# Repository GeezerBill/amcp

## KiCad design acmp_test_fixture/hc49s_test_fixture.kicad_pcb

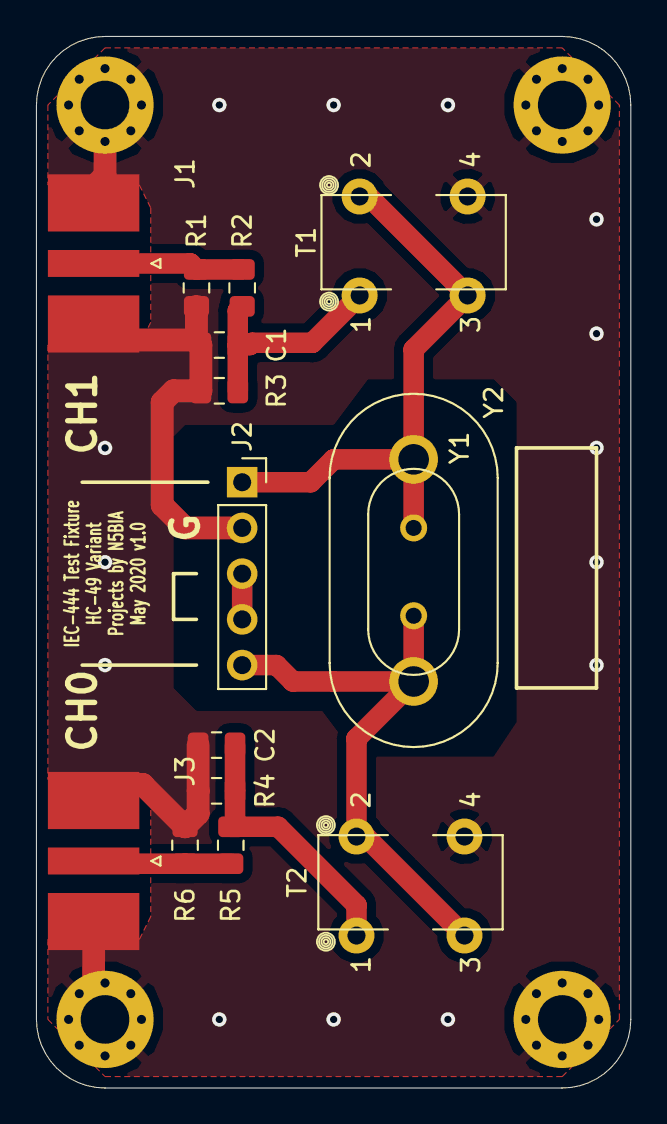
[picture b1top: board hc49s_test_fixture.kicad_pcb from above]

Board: 2 copper layers, 33.0 x 58.4 mm, 19 parts (0 on the bottom side), 8 nets.

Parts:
C1, C2: omit; C_0805_2012Metric_Pad1.15x1.40mm_HandSolder
J1, J3: SMA; SMA_EdgeMount
J2: 5 pos sip socket; PinSocket_1x05_P2.54mm_Vertical
M1, M2, M3, M4: MountingHole; MountingHole_2.7mm_Pad_Via
R1, R2, R3, R4, R5, R6: see table; R_0805_2012Metric_Pad1.15x1.40mm_HandSolder
T1, T2: Toroid; Transformer_Toroid_Vertical_L10.0mm_W5.0mm_T37
Y1: HS-49S; Crystal_HC49-4H_Vertical
Y2: HS-49S; Crystal_HC33-U_Vertical

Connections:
/zi: J1.1, R1.1, R2.2
/zi12.5: J2.1, T1.2, T1.3, Y1.1, Y2.1
/zi50: C1.1, R2.1, R3.1, T1.1
/zo: J3.1, R5.1, R6.1
/zo12.5: J2.5, T2.2, T2.3, Y1.2, Y2.2
/zo50: C2.1, R4.1, R5.2, T2.1
GND: C1.2, C2.2, J1.2, J2.2, J3.2, M1.1, M2.1, M3.1, M4.1, R1.2, R3.2, R4.2, R6.2, T1.4, T2.4
unnamed: J2.3, J2.4

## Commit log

2020-05-31 release to public via OSH Park
    Version 1.0 published on OSH Park and n5bia.net. As released for general distribution on nanoVNA group on groups.io
2020-05-31 Rename acmp_test_fixture/hc49s_test_fixture.net to acmp_test_fixture/hc49s_n5bia/hc49s_test_fixture.net
2020-05-31 initial commit - moving files to subfolder
